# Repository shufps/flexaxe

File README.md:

# flexaxe
repository for flex*axe project

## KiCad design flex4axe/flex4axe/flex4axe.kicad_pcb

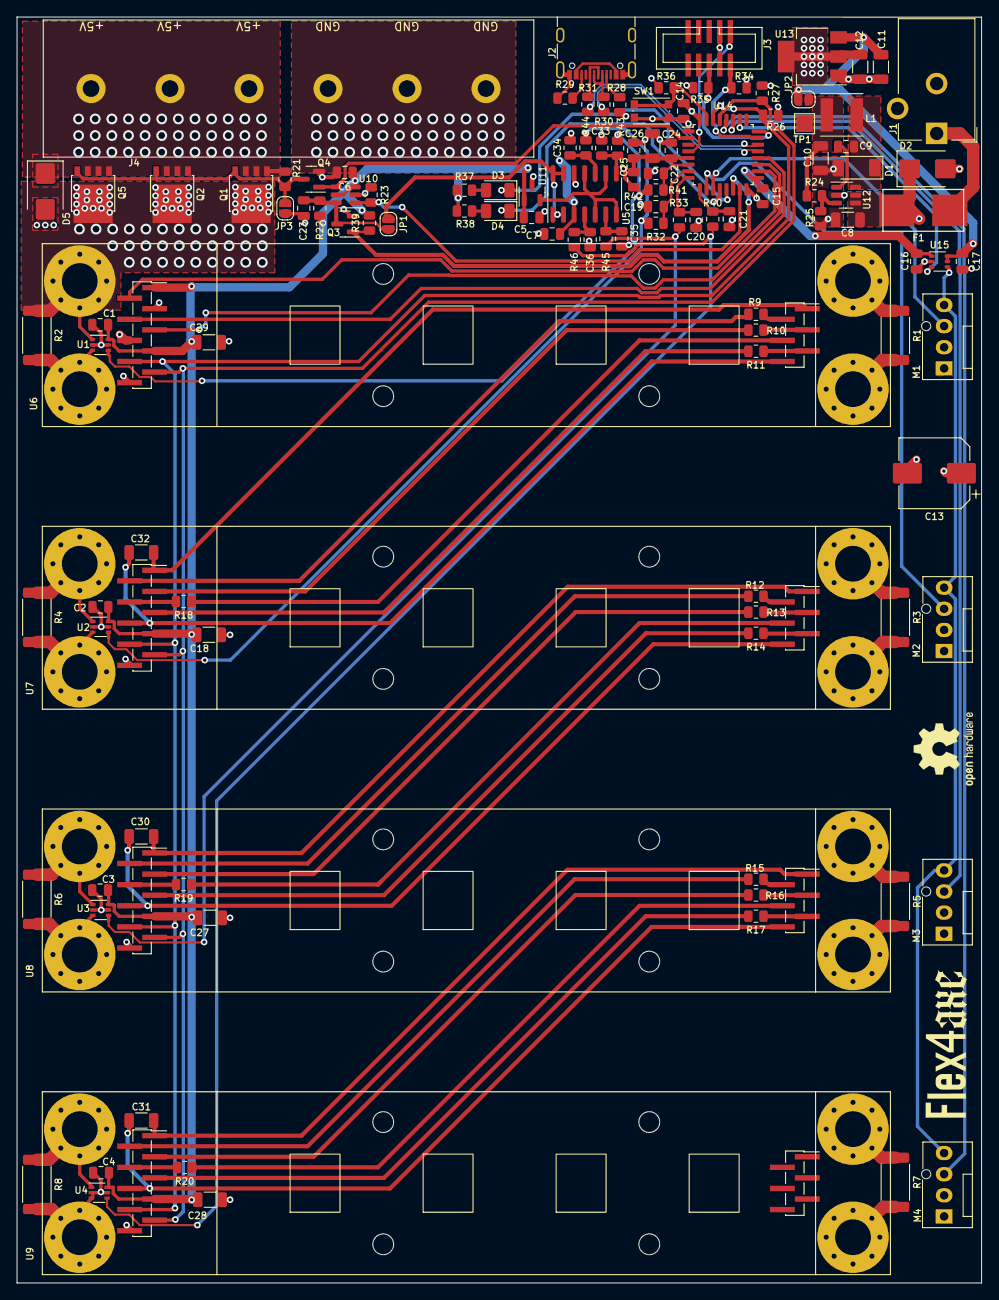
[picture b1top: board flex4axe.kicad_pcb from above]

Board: 4 copper layers, 116.0 x 152.3 mm, 122 parts (0 on the bottom side), 89 nets.

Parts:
C1, C2, C3, C4, C5, C6, C7, C14, C15, C16, C17, C19, C20, C21, C22, C23, C24: 100n; C_0805_2012Metric
C8, C11, C18, C26, C27, C28, C29, C30, C31, C32: 10µ/50V; C_1206_3216Metric
C9: 10n/250V; C_0805_2012Metric
C10, C12: 22µ/16V; C_1206_3216Metric
C13: 330µ; CP_Elec_8x10
C25: 1µ; C_0805_2012Metric
C33, C34, C35, C36: -; R_0805_2012Metric
D1: PMEG4030EP,115; D_SOD-128
D2: SMBJ12A; D_SMB
D3, D4: LED; LED_1206_3216Metric
D5: SMBJ5.0A; D_SMB
F1: 0.5A; fuseholder_littlefuse_blok
J1: Barrel_Jack_Switch; BarrelJack_CUI_PJ-102AH_Horizontal
J2: USB_C_Receptacle_USB2.0; USB_C_Receptacle_GCT_USB4105-xx-A_16P_TopMnt_Horizontal
J3: SWD; PinHeader_IDC_2x05_P1.27mm_Vertical_SMD
J4: Conn_01x06; BARRIER-TERMINAL-ANYTEK
JP1, JP2, JP3: SolderJumper_2_Open; SolderJumper-2_P1.3mm_Open_RoundedPad1.0x1.5mm
L1: 4.7µH/2A/3A; L_Taiyo-Yuden_NR-50xx
M1, M2, M3, M4: Fan_4pin; FanPinHeader_1x04_P2.54mm_Vertical
Q1, Q2, Q5: TPH1R712MD,L1Q; LFPAK56
Q3, Q4: BSS138; SOT-23
R1, R2, R3, R4, R5, R6, R7, R8: 1; R_2512_6332Metric
R9, R10, R11, R12, R13, R14, R15, R16, R17, R18, R19, R20, R30, R31, R42: 22; R_0805_2012Metric
R21, R22, R23, R34, R35, R39: 10k; R_0805_2012Metric
R24: 84.5k; R_0805_2012Metric
R25: 16.3k; R_0805_2012Metric
R26, R27: 1.5k; R_0805_2012Metric
R28, R29: 5.1k; R_0805_2012Metric
R32, R33, R40, R41: 1k; R_0805_2012Metric
R36: 100k; R_0805_2012Metric
R37, R38: 560; R_0805_2012Metric
R43, R44, R45, R46: 0; R_0805_2012Metric
SW1: boot; SW_Push_1P1T_NO_CK_KMR2
TP1: 3V3; TestPoint_Pad_2.0x2.0mm
U1, U2, U3, U4: INA500DCK; SOT-363_SC-70-6
U5: LM339; SOIC-14_3.9x8.7mm_P1.27mm
U6: U6; FLEXAXE
U7: U7; FLEXAXE
U8: U8; FLEXAXE
U9: U9; FLEXAXE
U10: 74LVC1G175; SOT-23-6
U11: ISL21080CIH315Z-TK; SOT-23
U12: AP3211; SOT-23-6
U13: 1117-3.3; SOT-223-3_TabPin2
U14: STM32L072KZT6; LQFP-32_7x7mm_P0.8mm
U15: TXU0101; SOT-363_SC-70-6

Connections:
+3V3: C1.1, C2.1, C3.1, C4.1, C5.1, C6.1, C7.1, C12.1, C14.1, C15.1, C16.1, C18.1, C27.1, C28.1, C29.1, R22.2, R26.1, R27.1, R34.2, R37.1, R38.1, R39.2, R42.2, SW1.2, U1.6 (V+), U2.6 (V+), U3.6 (V+), U4.6 (V+), U5.3 (V+), U6.A1 (+V_IF), U6.A7 (+3V3_I2C), U7.A7 (+3V3_I2C), U8.A7 (+3V3_I2C), U9.A7 (+3V3_I2C), U10.3 (D), U10.5 (VCC), U11.1 (Vin), U13.2 (VO), U14.1 (VDD), U14.17 (VDD), U15.1 (VCCA)
+3V3A: C24.1, C25.1, C26.1, R42.1, U14.5 (VDDA)
+5V: C11.1, C17.1, JP2.2 (B), U13.3 (VI), U15.5 (OE), U15.6 (VCCB)
+5V_PWR: Q1.5 (D), Q2.5 (D), Q5.5 (D), R1.1, R2.1, U1.1 (IN+), U6.+ (+1V2_ASIC)
+5V_PWR_EXT: D5.1 (A1), J4.1, J4.2, J4.3, Q1.1 (S), Q1.2 (S), Q1.3 (S), Q2.1 (S), Q2.2 (S), Q2.3 (S), Q5.1 (S), Q5.2 (S), Q5.3 (S), R21.2
+12V: C8.1, C13.1, D2.1 (A1), F1.1, M1.2 (+), M2.2 (+), M3.2 (+), M4.2 (+), U12.4 (EN), U12.5 (IN)
/Power/PWR_EN: R23.2, U10.1 (C), U14.15 (PB1)
/Power/Q: Q4.1 (G), U10.4 (Q), U14.2 (PC14)
/flex/1.5V: U5.5 (+), U5.7 (+), U5.9 (+), U5.11 (+), U11.2 (Vout)
/flex/1V8_0: C32.1, U6.B1 (+1V8), U7.A1 (+V_IF)
/flex/1V8_1: C30.1, U7.B1 (+1V8), U8.A1 (+V_IF)
/flex/1V8_2: C31.1, U8.B1 (+1V8), U9.A1 (+V_IF)
/flex/BO_0: R10.2, U7.A3 (BI)
/flex/BO_1: R13.2, U8.A3 (BI)
/flex/BO_2: R16.2, U9.A3 (BI)
/flex/CO_0: R11.2, U7.A5 (CI)
/flex/CO_1: R14.2, U8.A5 (CI)
/flex/CO_2: R17.2, U9.A5 (CI)
/flex/GND_0: C32.2, U6.B6 (GND_ASIC), U7.A6 (GND_IF)
/flex/GND_1: C30.2, U7.B6 (GND_ASIC), U8.A6 (GND_IF)
/flex/GND_2: C31.2, U8.B6 (GND_ASIC), U9.A6 (GND_IF)
/flex/NRSTO_0: R9.2, U7.A2 (NRSTI)
/flex/NRSTO_1: R12.2, U8.A2 (NRSTI)
/flex/NRSTO_2: R15.2, U9.A2 (NRSTI)
/flex/PWM: M1.4 (PWM), M2.4 (PWM), M3.4 (PWM), M4.4 (PWM), U15.4 (BY)
/flex/RESET: U6.A2 (NRSTI), U14.18 (PA8)
/flex/RI_0: R18.1, U6.B4 (RI)
/flex/RI_1: R19.1, U7.B4 (RI)
/flex/RI_2: R20.1, U8.B4 (RI)
/flex/RXD: U6.A4 (RO), U14.20 (PA10)
/flex/SCL: R27.2, U6.A9 (SCL), U7.A9 (SCL), U8.A9 (SCL), U9.A9 (SCL), U14.29 (PB6)
/flex/SDA: R26.2, U6.A8 (SDA), U7.A8 (SDA), U8.A8 (SDA), U9.A8 (SDA), U14.30 (PB7)
/flex/SHUTDOWN: C23.1, JP1.2 (B), Q3.3 (D), R22.1, U10.6 (~CLR)
/flex/TACHO1: M1.3 (Tacho), U14.11 (PA5)
/flex/TACHO2: M2.3 (Tacho), U14.10 (PA4)
/flex/TACHO3: M3.3 (Tacho), U14.27 (PB4)
/flex/TACHO4: M4.3 (Tacho), U14.28 (PB5)
/flex/TXD: U6.A5 (CI), U14.19 (PA9)
/flex/V_FLEX1: R41.2, R43.1, U1.4 (OUT)
/flex/V_FLEX2: R32.2, R44.1, U2.4 (OUT)
/flex/V_FLEX3: R33.2, R45.1, U3.4 (OUT)
/flex/V_FLEX4: R40.2, R46.1, U4.4 (OUT)
/stm32/LED1: D4.1 (K), U14.12 (PA6)
/stm32/LED2: D3.1 (K), U14.13 (PA7)
/stm32/NRST: J3.1, U14.4 (NRST)
/stm32/PWM_3V3: U14.26 (PB3), U15.3 (A)
/stm32/SWCLK: J3.6, R35.2, U14.24 (PA14)
/stm32/SWDIO: J3.2, R34.1, U14.23 (PA13)
/stm32/USB_D+: R31.1, U14.22 (PA12)
/stm32/USB_D-: R30.1, U14.21 (PA11)
GND: C1.2, C2.2, C3.2, C4.2, C5.2, C6.2, C7.2, C8.2, C10.2, C11.2, C12.2, C13.2, C14.2, C15.2, C16.2, C17.2, C18.2, C19.2, C20.2, C21.2, C22.2, C23.2, C24.2, C25.2, C26.2, C27.2, C28.2, C29.2, C33.2, C34.2, C35.2, C36.2, D1.2 (A), D2.2 (A2), D5.2 (A2), J1.2, J1.3, J2.A1 (GND), J2.A12 (GND), J2.B1 (GND), J2.B12 (GND), J2.S1 (SHIELD), J3.3, J3.4, J4.4, J4.5, J4.6, JP3.1 (A), M1.1 (-), M2.1 (-), M3.1 (-), M4.1 (-), Q3.2 (S), Q4.2 (S), R7.2, R8.2, R23.1, R25.2, R28.1, R29.1, R35.1, R36.1, U1.2 (V-), U1.5 (REF), U2.2 (V-), U2.5 (REF), U3.2 (V-), U3.5 (REF), U4.2 (V-), U4.3 (IN-), U4.5 (REF), U5.12 (V-), U6.A3 (BI), U6.A6 (GND_IF), U6.A10 (GND_I2C), U7.A10 (GND_I2C), U8.A10 (GND_I2C), U9.- (GND_ASIC), U9.A10 (GND_I2C), U10.2 (GND), U11.3 (GND), U12.2 (GND), U13.1 (GND), U14.16 (VSS), U14.32 (VSS), U15.2 (GND)
unnamed: C9.2, D1.1 (K), L1.1, U12.6 (SW)
unnamed: D3.2 (A), R37.2
unnamed: D4.2 (A), R38.2
unnamed: F1.2, J1.1
unnamed: J2.A5 (CC1), R28.2
unnamed: J2.B5 (CC2), R29.2
unnamed: J2.A6 (D+), J2.B6 (D+), R31.2
unnamed: J2.A7 (D-), J2.B7 (D-), R30.2
unnamed: JP1.1 (A), U5.1, U5.2, U5.13, U5.14
unnamed: C10.1, JP2.1 (A), L1.2, R24.1, TP1.1
unnamed: JP3.2 (B), Q1.4 (G), Q2.4 (G), Q4.3 (D), Q5.4 (G), R21.1
unnamed: Q3.1 (G), R39.1, U14.14 (PB0)
unnamed: R1.2, R2.2, R3.1, R4.1, U1.3 (IN-), U2.1 (IN+), U6.- (GND_ASIC), U7.+ (+1V2_ASIC)
unnamed: R3.2, R4.2, R5.1, R6.1, U2.3 (IN-), U3.1 (IN+), U7.- (GND_ASIC), U8.+ (+1V2_ASIC)
unnamed: R5.2, R6.2, R7.1, R8.1, U3.3 (IN-), U4.1 (IN+), U8.- (GND_ASIC), U9.+ (+1V2_ASIC)
unnamed: C36.1, R46.2, U5.4 (-)
unnamed: C35.1, R45.2, U5.6 (-)
unnamed: C34.1, R44.2, U5.10 (-)
unnamed: C33.1, R43.2, U5.8 (-)
unnamed: R10.1, U6.B3 (BO)
unnamed: R11.1, U6.B5 (CO)
unnamed: R9.1, U6.B2 (NRSTO)
unnamed: R13.1, U7.B3 (BO)
unnamed: R14.1, U7.B5 (CO)
unnamed: R12.1, U7.B2 (NRSTO)
unnamed: R18.2, U7.A4 (RO)
unnamed: R16.1, U8.B3 (BO)
unnamed: R17.1, U8.B5 (CO)
unnamed: R15.1, U8.B2 (NRSTO)
unnamed: R19.2, U8.A4 (RO)
unnamed: R20.2, U9.A4 (RO)
unnamed: C9.1, U12.1 (BS)
unnamed: R24.2, R25.1, U12.3 (FB)
unnamed: R36.2, SW1.1, U14.31 (BOOT0)
unnamed: C22.1, R41.1, U14.6 (PA0)
unnamed: C19.1, R32.1, U14.7 (PA1)
unnamed: C20.1, R33.1, U14.8 (PA2)
unnamed: C21.1, R40.1, U14.9 (PA3)

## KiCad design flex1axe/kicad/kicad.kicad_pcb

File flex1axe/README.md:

# Flex1Axe
Testboard for 1 FlexAxe module.

**note**: The buck converter is actually to weak to drive a FlexAxe module at full 485MHz. 
300MHz works well. It's not recommended to manufacture the Flex1Axe for commercial use. Is't just for testing FlexAxe modules after assembly before they are put into voltage chaining on the Flex4Axe
to minimize risk of not properly soldered ASICs causing a bad voltage domain balancing that could, in worst case, kill other ASICs.

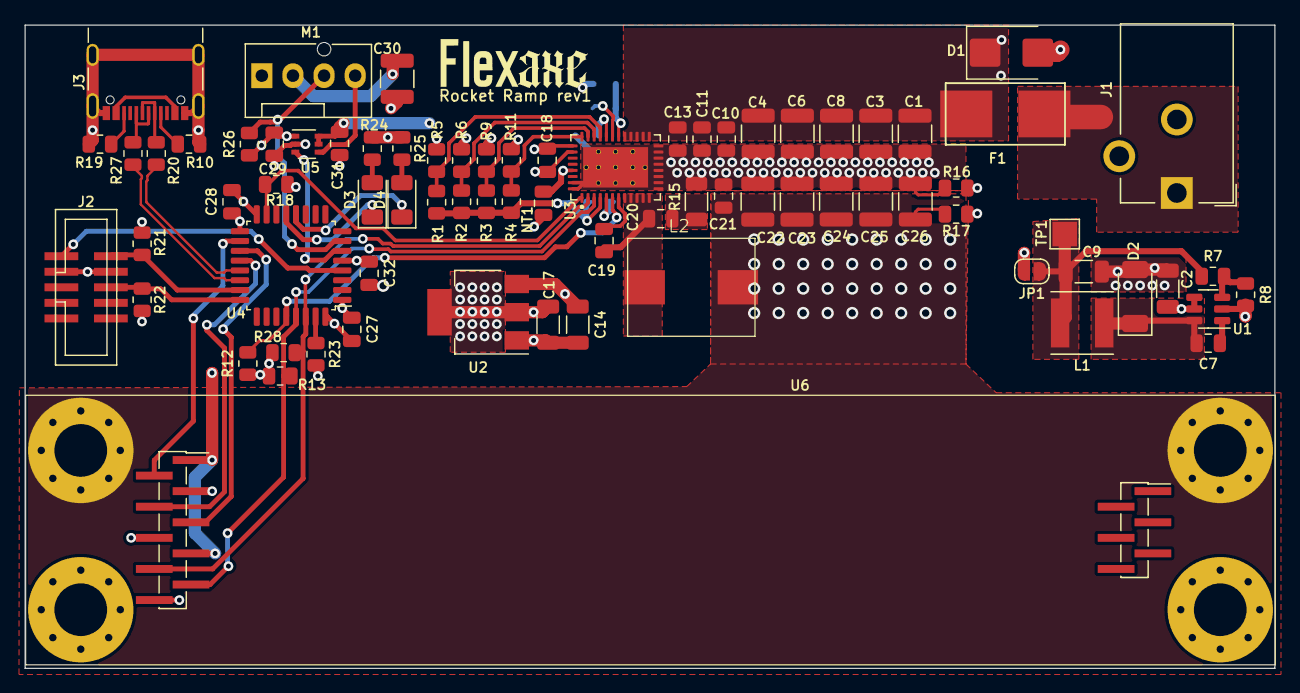
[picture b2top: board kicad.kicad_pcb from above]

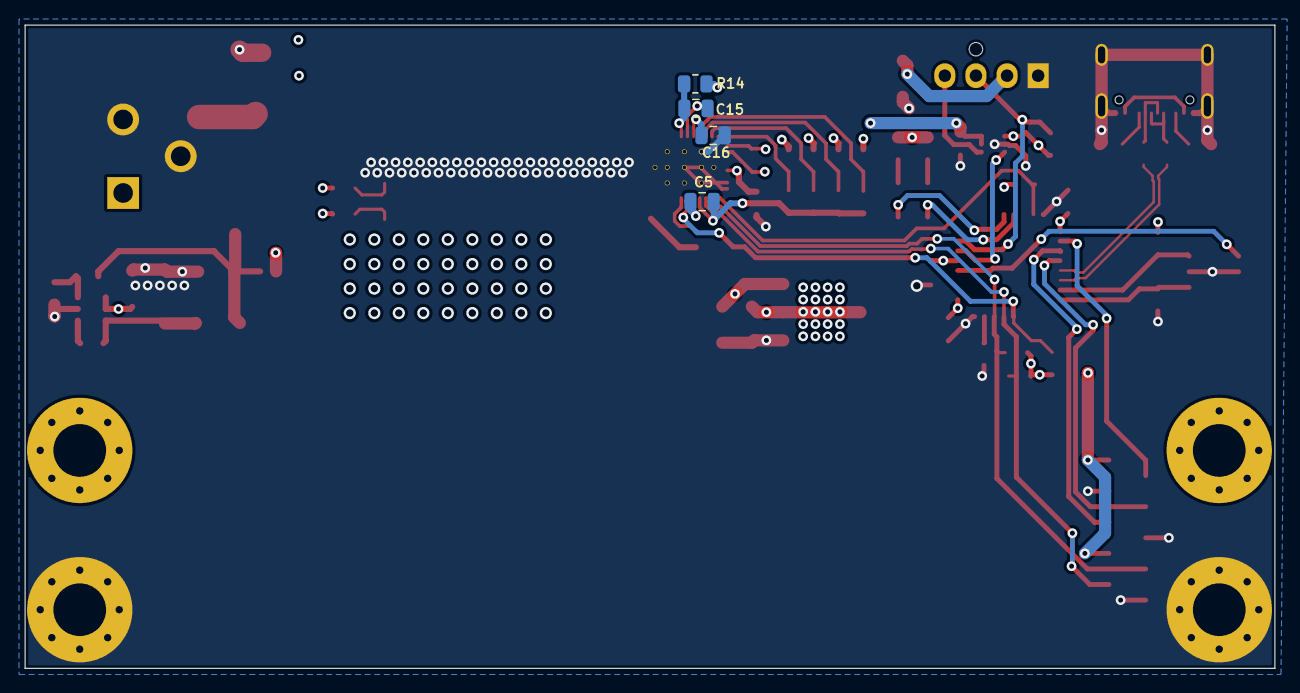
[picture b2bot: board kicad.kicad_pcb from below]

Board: 4 copper layers, 102.0 x 52.5 mm, 79 parts (4 on the bottom side), 47 nets.

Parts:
C1, C3: 100µ/16V; C_1210_3225Metric
C2, C14: 10µF/50V; C_1206_3216Metric
C4, C6, C8: 22µ/35V; C_1210_3225Metric
C5, C11, C15: 1µ; C_0805_2012Metric
C7: 10n/250V; C_0805_2012Metric
C9, C17: 22µ/16V; C_1206_3216Metric
C10: 4.7n; C_0805_2012Metric
C13, C21: 2.2n; C_0805_2012Metric
C16: 4.7µ; C_0805_2012Metric
C18: 100p; C_0805_2012Metric
C19, C27, C28, C29, C31, C32: 100n; C_0805_2012Metric
C20: 1n; C_0805_2012Metric
C22, C23: 47µ/6.3V; C_1210_3225Metric
C24, C25, C26: 330µ/4V; C_1210_3225Metric
C30: 22µ/25V; C_1210_3225Metric
D1: SMBJ12A; D_SMB
D2: PMEG4030EP,115; D_SOD-128
D3, D4: LED; LED_1206_3216Metric
F1: 5A; fuseholder_littlefuse_blok
J1: Barrel_Jack_Switch; BarrelJack_CUI_PJ-102AH_Horizontal
J2: SWD; PinHeader_IDC_2x05_P1.27mm_Vertical_SMD
J3: USB_C_Receptacle_USB2.0; USB_C_Receptacle_GCT_USB4105-xx-A_16P_TopMnt_Horizontal
JP1: SolderJumper_2_Open; SolderJumper-2_P1.3mm_Open_RoundedPad1.0x1.5mm
L1: 4.7µH/2A/3A; L_Taiyo-Yuden_NR-50xx
L2: 220nH; IFLR-4031GC-01-8x10
M1: Fan_4pin; FanPinHeader_1x04_P2.54mm_Vertical
NT1: NetTie_2; C_0805_2012Metric
R1, R3, R9: R_0805_2012Metric
R2: 15.4k; R_0805_2012Metric
R4: 17.8k; R_0805_2012Metric
R5, R6, R21, R22: 10k; R_0805_2012Metric
R7: 84.5k; R_0805_2012Metric
R8: 16.2k; R_0805_2012Metric
R10, R19: 5.1k; R_0805_2012Metric
R11: 26.1k; R_0805_2012Metric
R12, R13, R18, R28: 1.5k; R_0805_2012Metric
R14: 10R; R_0805_2012Metric
R15: 1R; R_1206_3216Metric
R16: 49.9R; R_0805_2012Metric
R17: 1.37k; R_0805_2012Metric
R20, R27: 22; R_0805_2012Metric
R23: 100k; R_0805_2012Metric
R24, R25: 560; R_0805_2012Metric
R26: 2.7k; R_0805_2012Metric
TP1: 3V3; TestPoint_Pad_2.0x2.0mm
U1: AP3211; SOT-23-6
U2: 1117-3.3; SOT-223-3_TabPin2
U3: TPS546D24ARVFR; LQFN40-CLIP
U4: STM32L052K6Tx; LQFP-32_7x7mm_P0.8mm
U5: TXU0101; SOT-363_SC-70-6
U6: U6; FLEXAXE

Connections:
+1V2: C21.1, C22.1, C23.1, C24.1, C25.1, C26.1, L2.2, R17.1, U6.+ (+1V2_ASIC)
+3V3: C17.1, C27.1, C28.1, C29.1, C32.1, R12.1, R13.1, R18.1, R21.2, R24.1, R25.1, R26.1, R28.1, U2.2 (VO), U4.1 (VDD), U4.5 (VDDA), U4.17 (VDD), U5.1 (VCCA), U6.A1 (+V_IF), U6.A7 (+3V3_I2C)
+5V: C14.1, C16.1, C31.1, JP1.2 (B), R14.2, U2.3 (VI), U3.28 (VDD5), U5.5 (OE), U5.6 (VCCB)
+12V: C1.1, C2.1, C3.1, C4.1, C6.1, C8.1, C10.1, C11.1, C13.1, C30.1, D1.1 (A1), F1.1, M1.2 (+), U1.4 (EN), U1.5 (IN), U3.21 (PVIN), U3.22 (PVIN), U3.23 (PVIN), U3.24 (PVIN), U3.25 (PVIN)
/Power/ALERT: R12.2, U3.6 (SMB_ALRT), U4.28 (PB5)
/Power/PGOOD: R18.2, U3.1 (PGD), U4.15 (PB1)
/flex/LED1: D4.1 (K), U4.12 (PA6)
/flex/LED2: D3.1 (K), U4.13 (PA7)
/flex/NRST: J2.1, U4.4 (NRST)
/flex/PWM: U4.6 (PA0), U5.3 (A)
/flex/RESET: U4.18 (PA8), U6.A2 (NRSTI)
/flex/RXD: U4.20 (PA10), U6.A4 (RO)
/flex/SCL: R13.2, U3.3 (PMB_CLK), U4.29 (PB6), U6.A9 (SCL)
/flex/SDA: R28.2, U3.2 (PMB_DATA), U4.30 (PB7), U6.A8 (SDA)
/flex/SWCLK: J2.6, R22.2, U4.24 (PA14)
/flex/SWDIO: J2.2, R21.1, U4.23 (PA13)
/flex/TACHO: M1.3 (Tacho), R26.2, U4.7 (PA1)
/flex/TXD: U4.19 (PA9), U6.A5 (CI)
/flex/USB_D+: R27.1, U4.22 (PA12)
/flex/USB_D-: R20.1, U4.21 (PA11)
GND: C1.2, C2.2, C3.2, C4.2, C6.2, C8.2, C9.2, C10.2, C11.2, C13.2, C14.2, C16.2, C17.2, C21.2, C22.2, C23.2, C24.2, C25.2, C26.2, C27.2, C28.2, C29.2, C30.2, C31.2, C32.2, D1.2 (A2), D2.2 (A), J1.2, J1.3, J2.3, J2.4, J3.A1 (GND), J3.A12 (GND), J3.B1 (GND), J3.B12 (GND), J3.S1 (SHIELD), M1.1 (-), NT1.2, R8.2, R10.1, R15.2, R16.2, R19.1, R22.1, R23.1, U1.2 (GND), U2.1 (GND), U3.13 (PGND), U3.14 (PGND), U3.15 (PGND), U3.16 (PGND), U3.17 (PGND), U3.18 (PGND), U3.19 (PGND), U3.20 (PGND), U3.39 (BCX_CLK), U3.40 (BCX_DAT), U3.41 (PAD), U4.16 (VSS), U4.32 (VSS), U5.2 (GND), U6.- (GND_ASIC), U6.A3 (BI), U6.A6 (GND_IF), U6.A10 (GND_I2C)
GNDA: C15.2, NT1.1, R5.1, R6.2, R9.1, R11.2, U3.27 (EN/UVLO), U3.37 (AGND)
unnamed: C19.2, C20.1, L2.1, U3.8 (SW), U3.9 (SW), U3.10 (SW), U3.11 (SW), U3.12 (SW)
unnamed: C20.2, R15.1
unnamed: C7.2, D2.1 (K), L1.1, U1.6 (SW)
unnamed: D3.2 (A), R24.2
unnamed: D4.2 (A), R25.2
unnamed: F1.2, J1.1
unnamed: J3.A5 (CC1), R10.2
unnamed: J3.B5 (CC2), R19.2
unnamed: J3.A6 (D+), J3.B6 (D+), R27.2
unnamed: J3.A7 (D-), J3.B7 (D-), R20.2
unnamed: C9.1, JP1.1 (A), L1.2, R7.1, TP1.1
unnamed: M1.4 (PWM), U5.4 (BY)
unnamed: C7.1, U1.1 (BS)
unnamed: R7.2, R8.1, U1.3 (FB)
unnamed: R3.2, R9.2, U3.31 (ADRSEL)
unnamed: C15.1, R14.1, U3.26 (AVIN)
unnamed: C19.1, U3.7 (BOOT)
unnamed: C5.1, R1.1, R2.1, R3.1, R4.1, U3.4 (BP1V5)
unnamed: C5.2, U3.5 (DRTN)
unnamed: C18.2, R16.1, U3.34 (GOSNS)
unnamed: R4.2, R11.1, U3.32 (MSEL1)
unnamed: R1.2, R5.2, U3.29 (MSEL2)
unnamed: C18.1, R17.2, U3.33 (VOSNS)
unnamed: R2.2, R6.1, U3.30 (VSEL)
unnamed: R23.2, U4.31 (BOOT0)

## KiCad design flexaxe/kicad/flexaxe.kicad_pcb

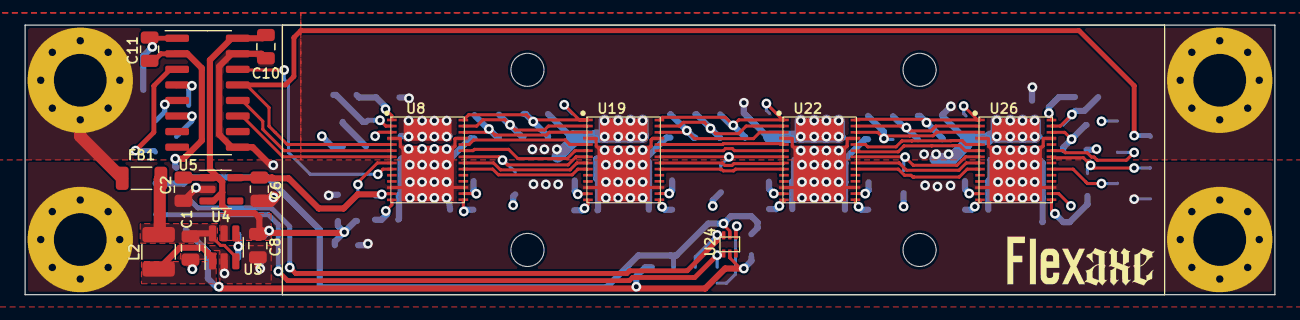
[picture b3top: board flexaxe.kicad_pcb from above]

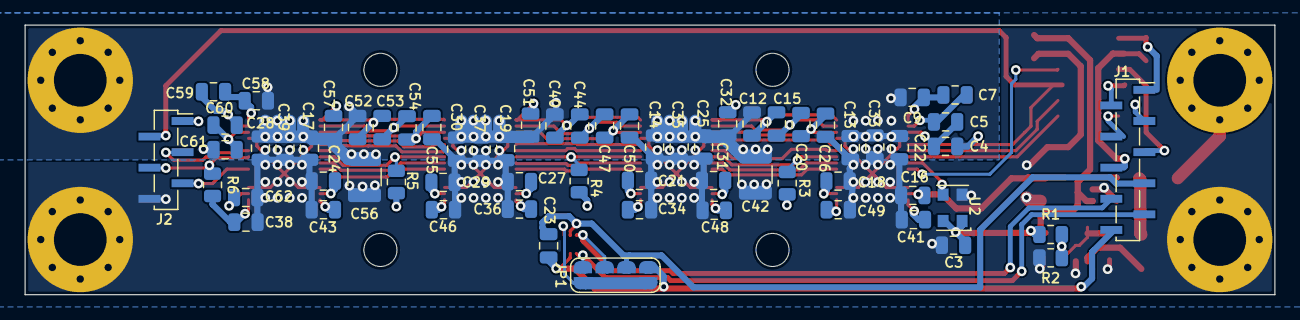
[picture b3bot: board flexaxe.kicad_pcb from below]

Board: 4 copper layers, 102.0 x 22.0 mm, 85 parts (65 on the bottom side), 56 nets.

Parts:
C1, C8, C13, C14, C17, C19: 10µ/16V; C_0805_2012Metric
C2, C3, C10, C11, C23, C33, C35, C37, C39: 100n; C_0805_2012Metric
C4, C5, C6, C7, C9, C12, C15, C16, C18, C20, C21, C22, C24, C25, C26, C27, C28, C29, C30, C31, C32, C34, C36, C38, C40, C41, C43, C44, C46, C47, C48, C49, C50, C51, C52, C53, C54, C55, C57, C58, C59, C60, C61, C62: 1µ; C_0805_2012Metric
C42, C56: 330µ/4V; C_1210_3225Metric
FB1: 600R@100MHz; L_1206_3216Metric
H1, H3: 1.2V; MountingHole_4.3mm_M4_Pad_Via
H2, H4: GND; MountingHole_4.3mm_M4_Pad_Via
J1: Conn_01x10; PinSocket_1x10_P1.27mm_Vertical_SMD_Pin1Right
J2: Conn_01x06; PinSocket_1x06_P1.27mm_Vertical_SMD_Pin1Right
JP1: SolderJumper_4_to_1; SolderJumper-4_to_1_P1.3mm_Open_RoundedPad1.0x1.5mm
L2: 4.7µH; L_1210_3225Metric
R1: 121k; R_0805_2012Metric
R2: 46.4k; R_0805_2012Metric
R3, R4, R5, R6: 10k; R_0805_2012Metric
U2: 25MHz; Oscillator_SMD_EuroQuartz_XO32-4Pin_3.2x2.5mm
U3: TPS61071; SOT-23-6
U4: NCP114ASN080T1G; SOT-23-5
U5: ADUM141E0BRZ-RL7; SOIC-16_3.9x9.9mm_P1.27mm
U8, U19, U22, U26: BM1366_mode1; BM1366
U24: TMP1075; TMP1075-DRL

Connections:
+0V8: C6.1, C16.2, C18.2, C21.2, C24.2, C27.2, C29.2, C31.2, C62.2, U4.5 (OUT), U8.13 (VDDIO_08_0), U8.16 (VDDIO_08_1), U19.13 (VDDIO_08_0), U19.16 (VDDIO_08_1), U22.13 (VDDIO_08_0), U22.16 (VDDIO_08_1), U26.13 (VDDIO_08_0), U26.16 (VDDIO_08_1)
+1V2: C9.2, C12.1, C13.1, C14.1, C17.1, C19.1, C22.1, C25.1, C28.1, C30.1, C32.2, C33.1, C35.1, C37.1, C39.1, C40.1, C42.1, C51.2, C52.1, C56.1, C57.2, C58.1, FB1.1, H1.1, H3.1, U8.29 (VDD), U19.29 (VDD), U22.29 (VDD), U26.29 (VDD)
+1V8: C2.1, C3.1, C8.1, C10.1, C34.1, C36.1, C38.1, C41.1, C43.1, C46.1, C48.1, C49.1, J2.1, R1.1, R3.2, R4.2, R5.2, R6.2, U2.1 (Standby), U2.4 (VDD), U3.5 (VOUT), U4.1 (IN), U4.3 (EN), U5.16 (VDD2), U8.14 (VDDIO_18_0), U8.15 (VDDIO_18_1), U19.14 (VDDIO_18_0), U19.15 (VDDIO_18_1), U22.14 (VDDIO_18_0), U22.15 (VDDIO_18_1), U26.14 (VDDIO_18_0), U26.15 (VDDIO_18_1)
+3V3_EXT: C23.1, J1.7, JP1.4 (B), U24.5 (V+)
+V_IF: C11.1, J1.1, U5.1 (VDD1)
/BI: U5.12 (VOC), U8.6 (BI)
/BO: J2.3, U26.23 (BO)
/CI: U5.14 (VOA), U8.9 (CI)
/CLKI: U2.3 (Out), U8.8 (CLKI)
/CO: J2.5, U26.20 (CO)
/IF_BI: J1.3, U5.5 (VIC)
/IF_CI: J1.5, U5.3 (VIA)
/IF_NRSTI: J1.2, U5.4 (VIB)
/IF_RO: J1.4, U5.6 (VOD)
/NRSTI: J2.2, U5.13 (VOB), U8.5 (NRSTI)
/RI: J2.4, R6.1, U26.22 (RI)
/RO: U5.11 (VID), U8.7 (RO)
/SCL2: J1.9, JP1.2 (B), U24.1 (SCL)
/SDA2: J1.8, JP1.3 (B), U24.6 (SDA)
GND: C1.2, C2.2, C3.2, C4.1, C6.2, C8.2, C10.2, C13.2, C14.2, C16.1, C17.2, C18.1, C19.2, C21.1, C22.2, C24.1, C25.2, C26.2, C27.1, C28.2, C29.1, C30.2, C31.1, C33.2, C34.2, C35.2, C36.2, C37.2, C38.2, C39.2, C41.2, C42.2, C43.2, C46.2, C48.2, C49.2, C50.2, C55.2, C56.2, C61.2, C62.1, H2.1, H4.1, J2.6, R2.2, U2.2 (GND), U3.2 (GND), U4.2 (GND), U5.9 (GND2), U5.15 (GND2), U8.4 (VSS), U8.12 (PLL_VSS), U8.17 (VSS), U8.25 (VSS), U8.30 (GND), U19.4 (VSS), U19.12 (PLL_VSS), U19.17 (VSS), U19.25 (VSS), U19.30 (GND), U22.4 (VSS), U22.12 (PLL_VSS), U22.17 (VSS), U22.25 (VSS), U22.30 (GND), U26.4 (VSS), U26.12 (PLL_VSS), U26.17 (VSS), U26.25 (VSS), U26.30 (GND)
GND_EXT: C23.2, J1.10, JP1.5 (B), U24.2 (GND)
GND_IF: C11.2, J1.6, U5.2 (GND1), U5.8 (GND1)
unnamed: JP1.1 (A), U24.4 (A0)
unnamed: C1.1, FB1.2, L2.1, U3.3 (EN), U3.6 (VIN)
unnamed: L2.2, U3.1 (SW)
unnamed: R1.2, R2.1, U3.4 (VFB)
unnamed: C7.2, C9.1, U8.1 (VDD1_0)
unnamed: C5.2, C7.1, U8.2 (VDD2_0)
unnamed: C4.2, C5.1, U8.3 (VDD3_0)
unnamed: U8.23 (BO), U19.6 (BI)
unnamed: U19.23 (BO), U22.6 (BI)
unnamed: U8.20 (CO), U19.9 (CI)
unnamed: U8.21 (CLKO), U19.8 (CLKI)
unnamed: U19.21 (CLKO), U22.8 (CLKI)
unnamed: U19.20 (CO), U22.9 (CI)
unnamed: U8.24 (NRSTO), U19.5 (NRSTI)
unnamed: U19.24 (NRSTO), U22.5 (NRSTI)
unnamed: R4.1, U19.22 (RI), U22.7 (RO)
unnamed: R3.1, U8.22 (RI), U19.7 (RO)
unnamed: C12.2, C15.2, C32.1, U8.28 (VDD1_1), U19.1 (VDD1_0)
unnamed: C40.2, C44.1, C51.1, U19.28 (VDD1_1), U22.1 (VDD1_0)
unnamed: C15.1, C20.1, U8.27 (VDD2_1), U19.2 (VDD2_0)
unnamed: C44.2, C47.1, U19.27 (VDD2_1), U22.2 (VDD2_0)
unnamed: C20.2, C26.1, U8.26 (VDD3_1), U19.3 (VDD3_0)
unnamed: C47.2, C50.1, U19.26 (VDD3_1), U22.3 (VDD3_0)
unnamed: U22.23 (BO), U26.6 (BI)
unnamed: U22.21 (CLKO), U26.8 (CLKI)
unnamed: U22.20 (CO), U26.9 (CI)
unnamed: U22.24 (NRSTO), U26.5 (NRSTI)
unnamed: R5.1, U22.22 (RI), U26.7 (RO)
unnamed: C52.2, C53.1, C57.1, U22.28 (VDD1_1), U26.1 (VDD1_0)
unnamed: C53.2, C54.1, U22.27 (VDD2_1), U26.2 (VDD2_0)
unnamed: C54.2, C55.1, U22.26 (VDD3_1), U26.3 (VDD3_0)
unnamed: C58.2, C59.1, U26.28 (VDD1_1)
unnamed: C59.2, C60.1, U26.27 (VDD2_1)
unnamed: C60.2, C61.1, U26.26 (VDD3_1)

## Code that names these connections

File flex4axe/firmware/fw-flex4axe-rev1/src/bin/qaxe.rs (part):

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impl From<QControl> for Control {
    fn from(value: QControl) -> Self {
        Control {
            led2: value.led2 == 1,
            pwm: [value.pwm1, value.pwm2, value.pwm3, value.pwm4],
        }
    }
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
    let p = embassy_stm32::init(config);

    let driver = Driver::new(p.USB, Irqs, p.PA12, p.PA11);

    // Create embassy-usb Config
    let mut config = embassy_usb::Config::new(0xc0de, 0xcafe);
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    static RX_BUF: StaticCell<[u8; 256]> = StaticCell::new();
    let rx_buf = &mut RX_BUF.init([0; 256])[..];

    let usart = BufferedUart::new(p.USART1, Irqs, p.PA10, p.PA9, tx_buf, rx_buf, config).unwrap();
    let (mut tx_ctrl, mut rx_ctrl) = usart.split();

    // Run the USB device.
    let usb_fut = usb.run();

    let pwr_en = Output::new(p.PB1, Level::Low, Speed::Low);
    let pwr_sdn = Output::new(p.PB0, Level::High, Speed::Low);
    let pwr_enabled = Input::new(p.PC14, Pull::None);
    let pgood_led = Output::new(p.PA6, Level::High, Speed::Low);
    let led2 = Output::new(p.PA7, Level::High, Speed::Low);

    let reset = Output::new(p.PA8, Level::Low, Speed::Low);

    let ch2 = PwmPin::new_ch2(p.PB3, OutputType::PushPull);
    let mut pwm1 = SimplePwm::new(
        p.TIM2,
        None,
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
    let i2c = I2c::new(
        p.I2C1,
        p.PB6,
        p.PB7,
        Irqs,
        NoDma,
        NoDma,
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    adc.set_sample_time(SampleTime::CYCLES160_5);

    let mut vrefint = adc.enable_vref(&mut Delay);
    let mut adc_pin_domain1 = p.PA0;
    let mut adc_pin_domain2 = p.PA1;
    let mut adc_pin_domain3 = p.PA2;
    let mut adc_pin_domain4 = p.PA3;

    let vrefint_sample = adc.read(&mut vrefint).await;

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    Control = 1,
    Status = 2,
    Reset = 3,
    Shutdown = 4,
    PowerOn = 5,
}

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
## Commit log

2024-03-14 Create LICENSE
2024-03-15 flex1axe testboard initial commit
2025-12-29 forgot to push the 4 flex version back then
